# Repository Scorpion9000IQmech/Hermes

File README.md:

# MORSE DECODER
---
I made a hermes project with the sensor, I kept it simple with only detected or not, instead of proximity values, so I could make it a morse decoder

### How it works
---
If input is less than 1.5 second it inputs dot, longer inputs dash, longer than 4 makes a space to end the input of ONE letter, longer than 6 ends the word
it then decodes it onto the screen, and plays back the code on the LED in morse, as well as plays functions that are added, as of now a simple play song by the code SONG, is added with simple buzzer noises

### images
---

### case
---

### I WILL BE PAYING FOR IT MYSELF
## BOM
---
| Parts | COST | LINK |
|-------|------|------|
| Buzzers 10 peice | 1.58 USD | [AliExpress](https://ar.aliexpress.com/item/1005008165091345.html?spm=a2g0o.productlist.main.8.3c86xKOixKOitP&aem_p4p_detail=202604270416102094164706196300001174606&algo_pvid=e2f0ab90-6a1b-48cf-8a82-a7af61c8c830&algo_exp_id=e2f0ab90-6a1b-48cf-8a82-a7af61c8c830-7&pdp_ext_f=%7B"order"%3A"139"%2C"spu_best_type"%3A"price"%2C"eval"%3A"1"%2C"fromPage"%3A"search"%7D&pdp_npi=6%40dis%21USD%211.58%211.58%21%21%2110.75%2110.75%21%402140ec5d17772885701743231ef38d%2112000044055302230%21sea%21OM%216453760668%21X%211%210%21n_tag%3A-29911%3Bd%3A4b15dde3%3Bm03_new_user%3A-29895&curPageLogUid=FBDDN1ZaPHbf&utparam-url=scene%3Asearch%7Cquery_from%3A%7Cx_object_id%3A1005008165091345%7C_p_origin_prod%3A&search_p4p_id=202604270416102094164706196300001174606_2) |
| XIAO RP2040 | 6.31 USD | [AliExpress](https://ar.aliexpress.com/item/1005006593701624.html?spm=a2g0o.productlist.main.1.594e72a0k3wotb&algo_pvid=3994ba39-1c0d-4fbb-9548-68c0d8941582&algo_exp_id=3994ba39-1c0d-4fbb-9548-68c0d8941582-0&pdp_ext_f=%7B"order"%3A"447"%2C"eval"%3A"1"%2C"fromPage"%3A"search"%7D&pdp_npi=6%40dis%21USD%216.31%214.67%21%21%216.31%214.67%21%402140ec5d17772896468825754ef38f%2112000039072595754%21sea%21OM%216453760668%21X%211%210%21n_tag%3A-29911%3Bd%3A4b15dde3%3Bm03_new_user%3A-29895&curPageLogUid=k188lO9MGhtl&utparam-url=scene%3Asearch%7Cquery_from%3A%7Cx_object_id%3A1005006593701624%7C_p_origin_prod%3A) |
| LED | --- | from my personal electronics kit, already had some |
| Resistors |---| also from my own kit |
| Capacitors |---| I have capacitors in my kit |
| connectors 0*8 |---| available in my kit |
| connectors 0*4 |--- | also available in my kit |
| VCNL36828P | $2.43 USD | [JLPCB](https://jlcpcb.com/partdetail/VishayIntertech-VCNL36828P/C19183990) |

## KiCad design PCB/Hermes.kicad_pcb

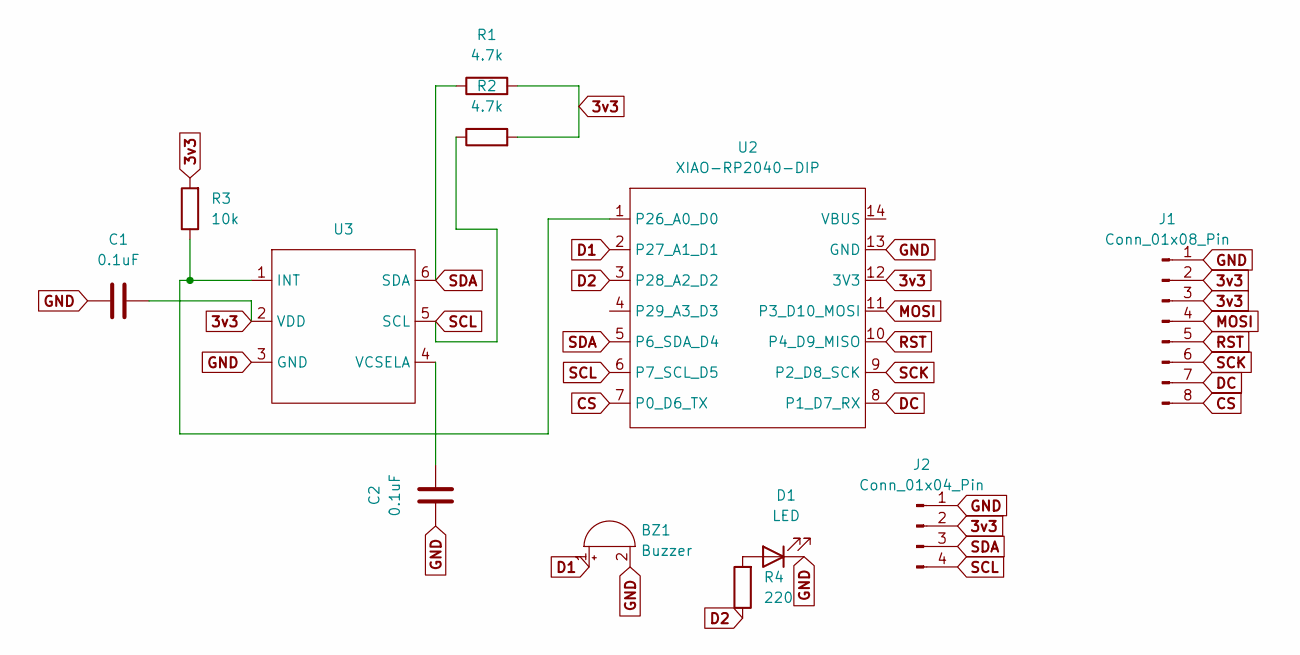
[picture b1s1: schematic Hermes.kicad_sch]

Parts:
BZ1: Buzzer; Buzzer_12x9.5RM7.6
C1, C2: 0.1uF; CP_Radial_D8.0mm_P5.00mm
D1: LED; LED_D5.0mm
J1: Conn_01x08_Pin; PinHeader_1x08_P2.54mm_Vertical
J2: Conn_01x04_Pin; PinHeader_1x04_P2.54mm_Vertical
R1, R2: 4.7k; R_Axial_DIN0207_L6.3mm_D2.5mm_P7.62mm_Horizontal
R3: 10k; R_Axial_DIN0207_L6.3mm_D2.5mm_P7.62mm_Horizontal
R4: 220; R_Axial_DIN0207_L6.3mm_D2.5mm_P7.62mm_Horizontal
U2: XIAO-RP2040-DIP
U3: DFN-6_L2.0-W1.0-P0.73-BL_VCNL36828P

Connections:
3v3: C1.1, J1.2, J1.3, J2.2, R1.2, R2.2, R3.2, U2.12 (3V3), U3.2 (VDD)
CS: J1.8, U2.7 (P0_D6_TX)
D1: BZ1.1 (+), U2.2 (P27_A1_D1)
D2: R4.1, U2.3 (P28_A2_D2)
DC: J1.7, U2.8 (P1_D7_RX)
GND: BZ1.2 (-), C1.2, C2.2, D1.1 (K), J1.1, J2.1, U2.13 (GND), U3.3 (GND)
MOSI: J1.4, U2.11 (P3_D10_MOSI)
unnamed: D1.2 (A), R4.2
unnamed: R3.1, U2.1 (P26_A0_D0), U3.1 (INT)
unnamed: C2.1, U3.4 (VCSELA)
RST: J1.5, U2.10 (P4_D9_MISO)
SCK: J1.6, U2.9 (P2_D8_SCK)
SCL: J2.4, R2.1, U2.6 (P7_SCL_D5), U3.5 (SCL)
SDA: J2.3, R1.1, U2.5 (P6_SDA_D4), U3.6 (SDA)

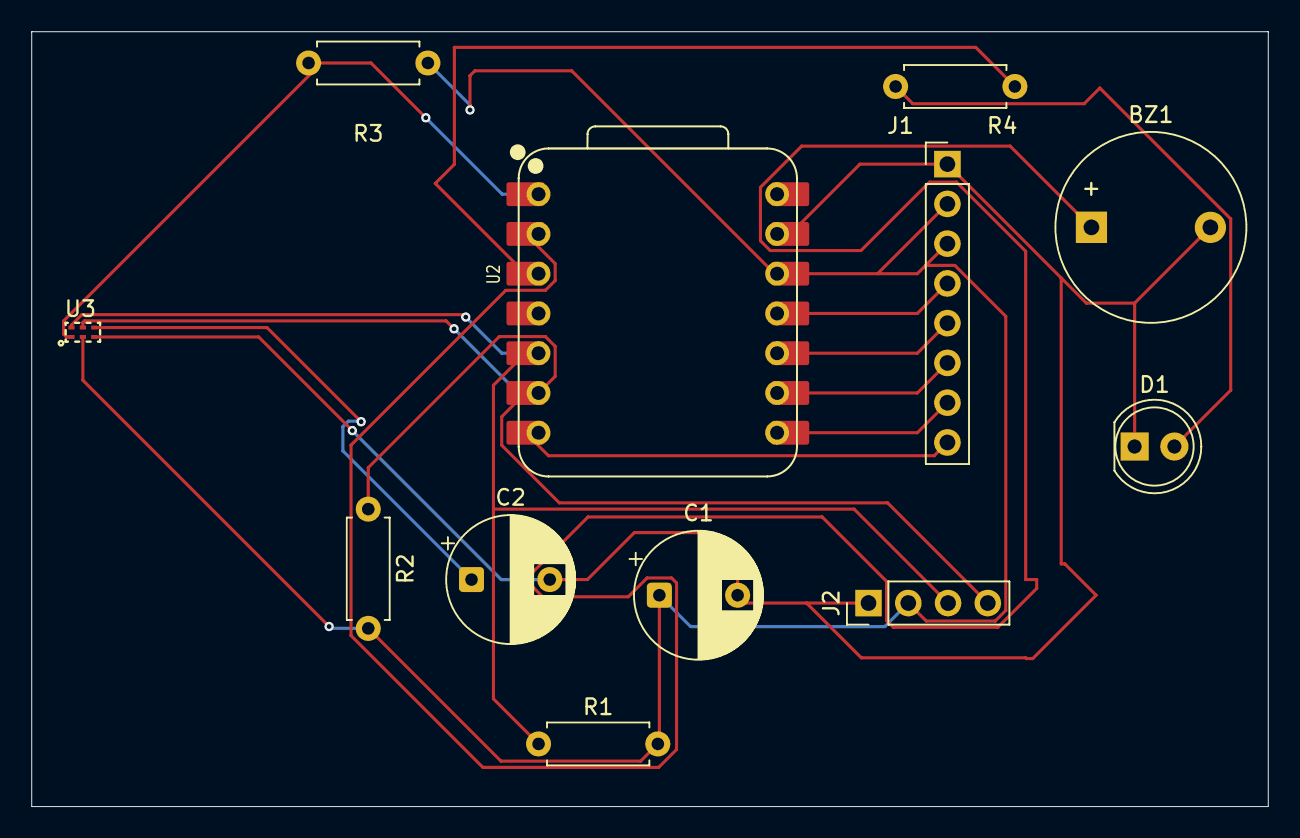
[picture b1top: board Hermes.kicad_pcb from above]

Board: 2 copper layers, 79.0 x 49.5 mm, 12 parts (0 on the bottom side), 14 nets.

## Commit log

2026-05-02 Rename Hermes.kicad_pcb to PCB/Hermes.kicad_pcb
2026-05-02 Rename Hermes.kicad_pro to PCB/Hermes.kicad_pro
2026-05-02 Rename Hermes.kicad_sch to PCB/Hermes.kicad_sch
2026-05-02 Rename MORSEDECODER.ino to DECODER CODE/MORSEDECODER.ino
2026-05-02 Rename MORSE CASE.step to open case/MORSE CASE.step
2026-05-02 Rename gerberNdrillFiles.rar to PCB/gerberNdrillFiles.rar
2026-05-02 Rename BIM.csv to BOM.csv
